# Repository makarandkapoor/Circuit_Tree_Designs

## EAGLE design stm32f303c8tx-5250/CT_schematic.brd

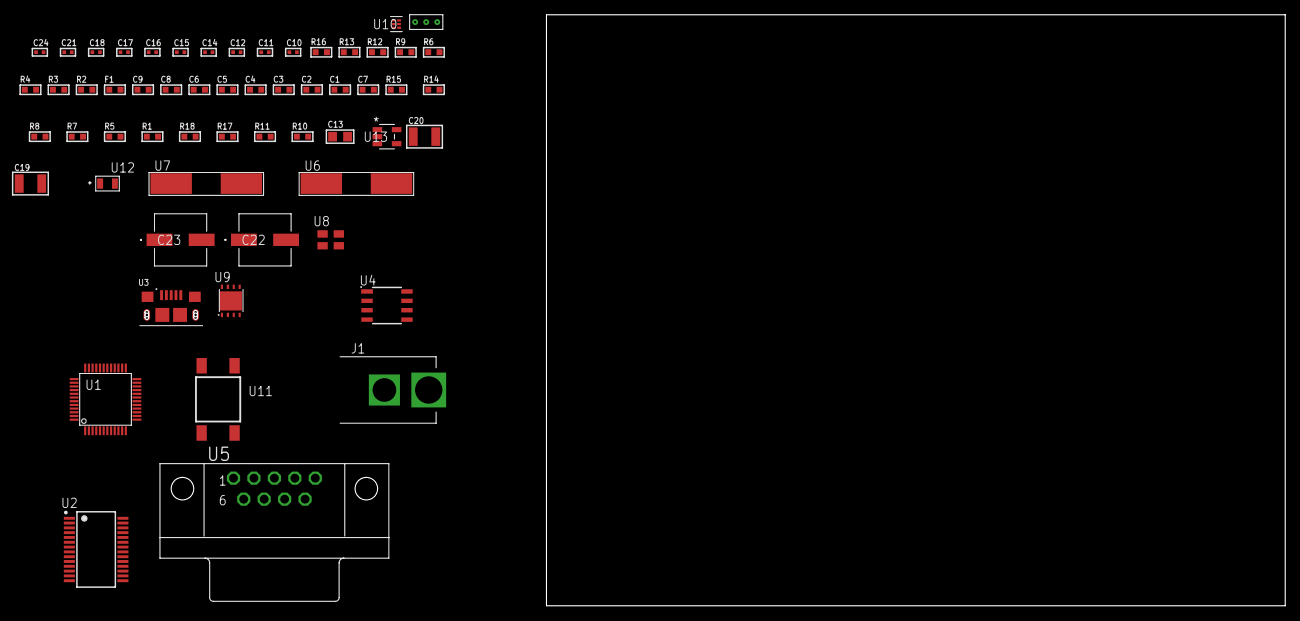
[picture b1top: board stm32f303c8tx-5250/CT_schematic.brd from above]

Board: 2 copper layers, 58 parts (0 on the bottom side), 38 nets, no tracks yet.

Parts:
C1, C9: 1e-06; C0603
C2, C3, C4, C5, C6: 1e-07; C0603
C7: 4.7e-06; C0603
C8: 1e-08; C0603
C10, C11: 1e-11; C0402
C12, C14, C15, C16, C21: 1e-07; C0402
C13: 4.7e-06; C0805
C17, C18, C24: 1e-08; C0402
C19, C20: 1e-05; C1210
C22, C23: 0.0001; EXV-9H
F1: 240.0; L0603
J1: PJ-037B; PJ-037B_PACKAGE
R1, R5, R7, R8, R14, R15: 10000.0; R0603
R2, R13: 1000.0; R0603
R3: 1600.5; R0603
R4, R6: 4700.0; R0603
R9: 120.0; R0603
R10, R11: 100000.0; R0603
R12: 2231.0; R0603
R16: 9100.0; R0603
R17: 680000.0; R0603
R18: 120000.0; R0603
U1: STM32F303C8T6; LQFP48
U2: FT232RL-REEL; SSOP-28
U3: 10118193-0001LF; FCI_10118193-0001LF
U4: SN65HVD230D; SOIC-8
U5: 182-009-113R531; 182-009-MALE
U6: ABLS-25.000MHZ-B2F-T
U7: ABLS-12.000MHZ-B4-T
U8: ASEK-32.768KHz-ECST; ASEK
U9: LP3878SDX-ADJ/NOPB; WSON-8
U10: TPS3895ADRYR; SON-6
U11: 4-1437565-2; SW_4-1437565-2
U12: Q65110A2395; LGM67K-G1J2-24-Z
U13: nc7sz125m5x; NC7SZ125M5X
U14: Dummy; DUMMY_PACKAGE_117

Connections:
CLK_CRYSTAL_U1_5: C10.1, U1.5, U6.1
CLK_CRYSTAL_U1_6: C11.1, U1.6, U6.2
CLK_CRYSTAL_U2_27: U2.27, U7.1
CLK_CRYSTAL_U2_28: U2.28, U7.2
CLK_U1_3: U1.3, U8.3
GND: C1.2, C2.2, C3.2, C4.2, C5.2, C6.2, C7.2, C8.2, C9.2, C10.2, C11.2, C12.2, C13.2, C14.2, C15.2, C16.2, C17.2, C18.2, C19.2, C20.2, C21.2, C22.2, C23.2, C24.2, J1.2, R2.2, R5.2, R8.2, R10.2, R13.2, R16.2, R18.2, U1.8, U1.23, U1.35, U1.47, U2.7, U2.18, U2.21, U2.25, U2.26, U3.5, U3.6, U3.7, U3.8, U3.9, U4.2, U5.5, U8.2, U9.3, U9.PAD, U10.2, U12.C, U13.1, U13.3, U14.1
NET_U1_7: R4.1, U1.7, U13.4
NET_U1_9: C8.1, C9.1, F1.1, U1.9
NET_U1_42: R3.1, U1.42, U12.A
NET_U1_43: R1.1, U1.43, U11.3, U11.4
NET_U1_44: R5.1, U1.44
NET_U2_14: R7.1, U2.14
NET_U2_17: C14.1, U2.17
NET_U2_19: R8.1, U2.19
NET_U3_1: R6.1, U3.1
NET_U3_2: U2.16, U3.2
NET_U3_3: U2.15, U3.3
NET_U4_6: R9.2, U4.6
NET_U4_8: R10.1, U4.8
NET_U5_2: R9.2, U4.6, U5.2
NET_U5_3: R9.1, U4.7, U5.3
NET_U9_1: C18.1, U9.1
NET_U9_6: R12.2, R13.1, U9.6
NET_U9_8: R11.1, U9.8
NET_U10_1: R15.1, R16.1, U10.1
NET_U10_3: R17.2, R18.1, U10.3
NET_U10_4: R14.1, U10.4, U13.2
NET_U11_1: R2.1, U11.1, U11.2
PROC_CAN_RX: U1.45, U4.4
PROC_CAN_TX: U1.46, U4.1
PROC_TIM1_CH1: U1.29, U14.3
PROC_TIM1_CH2N: U1.18, U14.2
PROC_USART1_CTS: U1.32, U2.3
PROC_USART1_RTS: U1.33, U2.11
PROC_USART1_RX: U1.31, U2.1
PROC_USART1_TX: U1.30, U2.5
VCC_S1_11V5: C19.1, C22.1, C23.1, J1.1, R11.2, U9.4
VCC_TIER1_3V3: C1.1, C2.1, C3.1, C4.1, C5.1, C6.1, C7.1, C12.1, C13.1, C15.1, C16.1, C17.1, C20.1, C21.1, C24.1, F1.2, R1.2, R3.2, R4.2, R7.2, R12.1, R14.2, R15.2, R17.1, U1.1, U1.24, U1.36, U1.48, U2.4, U2.20, U4.3, U8.4, U9.5, U10.6, U13.5

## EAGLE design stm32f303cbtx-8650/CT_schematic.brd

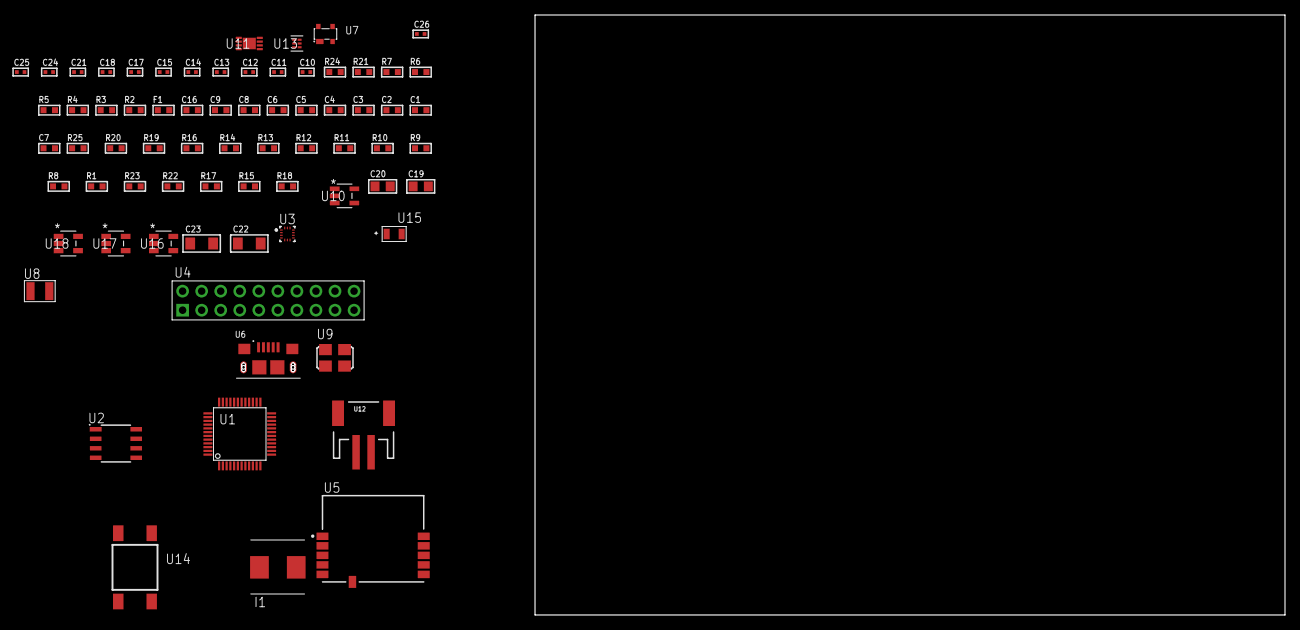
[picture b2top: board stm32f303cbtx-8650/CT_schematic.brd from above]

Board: 2 copper layers, 71 parts (0 on the bottom side), 41 nets, no tracks yet.

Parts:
C1, C9, C16: 1e-06; C0603
C2, C3, C4, C5, C6: 1e-07; C0603
C7: 4.7e-06; C0603
C8: 1e-08; C0603
C10, C11: 1e-11; C0402
C12, C18, C24, C25, C26: 1e-08; C0402
C13, C14, C15, C17, C21: 1e-07; C0402
C19, C20: 1e-05; C0805
C22, C23: 1e-05; C1206
F1: 240.0; L0603
I1: 2e-06; WE-HCI_7030/7040/7050
R1, R8, R9, R10, R11, R12, R13, R14, R19, R20, R25: 10000.0; R0603
R2: 1000.0; R0603
R3: 1600.5; R0603
R4, R5: 4700.0; R0603
R6, R7: 2200.0; R0603
R15: 100000.0; R0603
R16: 47000.0; R0603
R17: 220000.0; R0603
R18: 1000000.0; R0603
R21: 9100.0; R0603
R22: 680000.0; R0603
R23: 120000.0; R0603
R24: 2000.0; R0603
U1: STM32F303CBT6; LQFP48
U2: AT25020B-SSHL-T; SOIC-8
U3: BMC150; LGA14R35P5X6_200X200X100
U4: TST-110-05-T-D-RA
U5: SPBTLE-RF; XCVR_SPBTLE-RF
U6: 10118193-0001LF; FCI_10118193-0001LF
U7: prtr5v0u2ax; SOT143B
U8: ABS07-32.768KHZ-7-T
U9: ASFL1-25MHZ-NCS; ASFL1
U10: ltc3406es5; TSOT-23-5
U11: MCP73831T-2ACI/MC; DFN8_2X3MC
U12: S2B-PH-SM4-TB(LF)(SN); JST-2-SMD
U13: TPS3895ADRYR; SON-6
U14: 4-1437565-2; SW_4-1437565-2
U15: Q65110A2395; LGM67K-G1J2-24-Z
U16, U17, U18: nc7sz125m5x; NC7SZ125M5X

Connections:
CLK_CRYSTAL_U1_3: C10.1, U1.3, U8.1
CLK_CRYSTAL_U1_4: C11.1, U1.4, U8.2
CLK_U1_5: U1.5, U9.3
GND: C1.2, C2.2, C3.2, C4.2, C5.2, C6.2, C7.2, C8.2, C9.2, C10.2, C11.2, C12.2, C13.2, C14.2, C15.2, C16.2, C17.2, C18.2, C19.2, C20.1, C20.2, C21.2, C22.2, C23.2, C24.2, C25.2, C26.2, R2.2, R8.2, R15.2, R16.2, R17.2, R21.2, R23.2, R24.2, U1.8, U1.23, U1.35, U1.47, U2.4, U3.1, U3.6, U3.7, U3.9, U4.4, U4.6, U4.8, U4.10, U4.12, U4.14, U4.16, U4.18, U4.20, U5.6, U6.5, U6.6, U6.7, U6.8, U6.9, U7.1, U9.2, U10.2, U11.6, U11.9, U12.2, U13.2, U15.C, U16.2, U16.3, U17.1, U17.3, U18.1, U18.3
INPUT_USBPOWER_5V: C22.1, R25.2, U6.1, U7.4, U11.1, U11.2
NET_U1_7: R5.1, U1.7, U18.4
NET_U1_9: C8.1, C9.1, F1.1, U1.9
NET_U1_38: R6.1, U1.38, U3.11
NET_U1_43: R7.1, U1.43, U3.14
NET_U1_44: R8.1, U1.44
NET_U1_45: R3.1, U1.45, U15.A
NET_U1_46: R1.1, U1.46, U14.3, U14.4
NET_U2_3: R9.1, U2.3
NET_U2_7: R11.1, U2.7
NET_U5_11: R4.1, U5.11, U17.4
NET_U10_3: I1.1, U10.3
NET_U10_5: R17.1, R18.1, U10.5
NET_U10_ATNET_3: I1.2, R18.2
NET_U11_5: R25.1, U11.5
NET_U11_8: R24.1, U11.8
NET_U13_1: R20.1, R21.1, U13.1
NET_U13_3: R22.2, R23.1, U13.3
NET_U13_4: R19.1, U13.4, U16.4, U17.2, U18.2
NET_U14_1: R2.1, U14.1, U14.2
PROC_GPIO_TO_U5_SPI_IRQ: R16.1, U1.2, U5.4
PROC_SPI1_MISO: U1.16, U5.8
PROC_SPI1_MOSI: U1.17, U5.9
PROC_SPI1_NSS: R14.1, U1.14, U5.10
PROC_SPI1_SCK: R15.1, U1.15, U5.7
PROC_SPI2_MISO: U1.27, U2.2
PROC_SPI2_MOSI: U1.28, U2.5
PROC_SPI2_NSS: R10.1, U1.25, U2.1
PROC_SPI2_SCK: U1.26, U2.6
PROC_SYS_JTCK_SWCLK: U1.37, U4.9
PROC_SYS_JTDO_TRACESWO: U1.39, U4.13
PROC_SYS_JTMS_SWDIO: U1.34, U4.7
PROC_USB_DM: U1.32, U6.2, U7.3
PROC_USB_DP: U1.33, U6.3, U7.2
RST_OUT_U4_SRESET_B: R13.1, U4.15, U16.1
VCC_S1_3V7: C19.1, C23.1, U10.4, U11.3, U11.4, U12.1
VCC_TIER1_3V3: C1.1, C2.1, C3.1, C4.1, C5.1, C6.1, C7.1, C12.1, C13.1, C14.1, C15.1, C16.1, C17.1, C18.1, C20.2, C21.1, C24.1, C25.1, C26.1, F1.2, I1.2, R1.2, R3.2, R4.2, R5.2, R6.2, R7.2, R9.2, R10.2, R11.2, R12.1, R12.2, R13.2, R14.2, R18.2, R19.2, R20.2, R22.1, U1.1, U1.24, U1.36, U1.48, U2.8, U3.8, U3.10, U3.12, U3.13, U4.1, U5.5, U9.4, U13.6, U16.5, U17.5, U18.5

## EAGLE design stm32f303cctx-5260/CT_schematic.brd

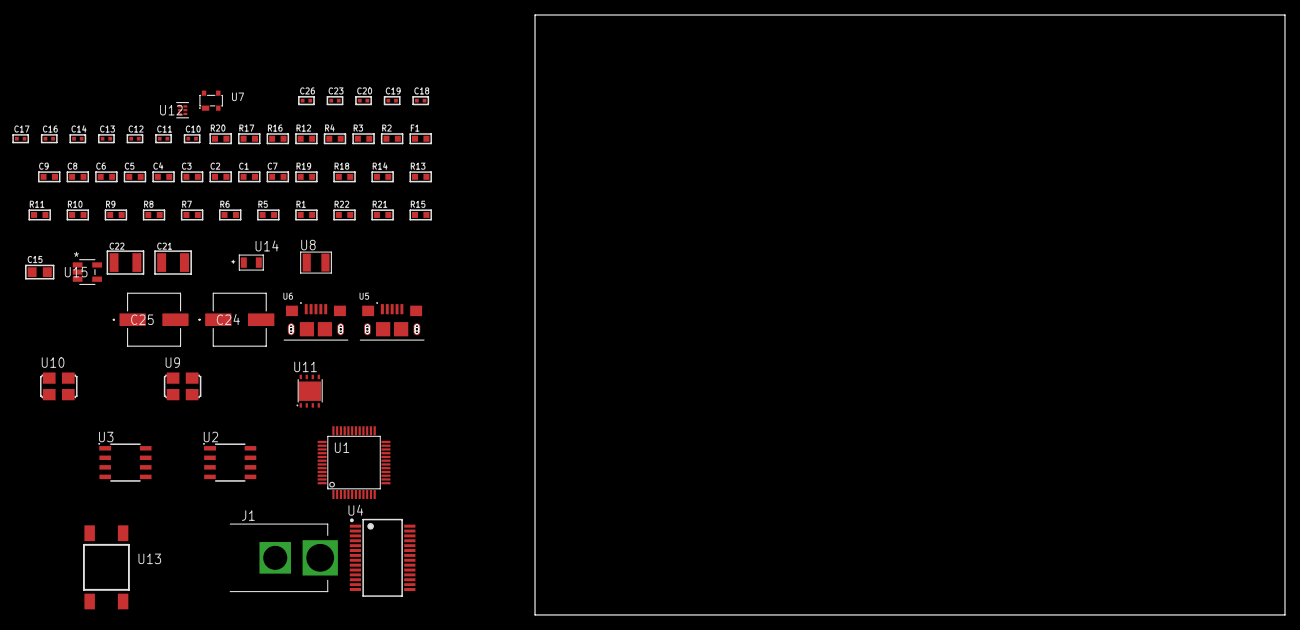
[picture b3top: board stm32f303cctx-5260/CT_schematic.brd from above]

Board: 2 copper layers, 65 parts (0 on the bottom side), 44 nets, no tracks yet.

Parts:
C1, C9: 1e-06; C0603
C2, C3, C4, C5, C6: 1e-07; C0603
C7: 4.7e-06; C0603
C8: 1e-08; C0603
C10, C11: 1e-11; C0402
C12, C13, C18, C19, C20, C26: 1e-08; C0402
C14, C16, C17, C23: 1e-07; C0402
C15: 4.7e-06; C0805
C21, C22: 1e-05; C1210
C24, C25: 0.0001; EXV-9H
F1: 240.0; L0603
J1: PJ-037B; PJ-037B_PACKAGE
R1, R5, R6, R7, R8, R9, R10, R11, R13, R14, R18, R19: 10000.0; R0603
R2, R17: 1000.0; R0603
R3: 1600.5; R0603
R4, R12: 4700.0; R0603
R15: 100000.0; R0603
R16: 2231.0; R0603
R20: 9100.0; R0603
R21: 680000.0; R0603
R22: 120000.0; R0603
U1: STM32F303CCT6; LQFP48
U2: AT25320B-SSHL-T; SOIC-8
U3: AT25512N-SH-T; SOIC-8
U4: FT232RL-REEL; SSOP-28
U5, U6: 10118193-0001LF; FCI_10118193-0001LF
U7: prtr5v0u2ax; SOT143B
U8: ABS07-32.768KHZ-7-T
U9: ASFL1-12MHZ-NCS; ASFL1
U10: ASFL1-25MHZ-NCS; ASFL1
U11: LP3878SDX-ADJ/NOPB; WSON-8
U12: TPS3895ADRYR; SON-6
U13: 4-1437565-2; SW_4-1437565-2
U14: Q65110A2395; LGM67K-G1J2-24-Z
U15: nc7sz125m5x; NC7SZ125M5X

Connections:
CLK_CRYSTAL_U1_3: C10.1, U1.3, U8.1
CLK_CRYSTAL_U1_4: C11.1, U1.4, U8.2
CLK_U1_5: U1.5, U10.3
CLK_U4_27: U4.27, U9.3
GND: C1.2, C2.2, C3.2, C4.2, C5.2, C6.2, C7.2, C8.2, C9.2, C10.2, C11.2, C12.2, C13.2, C14.2, C15.2, C16.2, C17.2, C18.2, C19.2, C20.2, C21.2, C22.2, C23.2, C24.2, C25.2, C26.2, J1.2, R2.2, R5.2, R14.2, R17.2, R20.2, R22.2, U1.8, U1.23, U1.35, U1.47, U2.4, U3.4, U4.7, U4.18, U4.21, U4.25, U4.26, U5.5, U5.6, U5.7, U5.8, U5.9, U6.5, U6.6, U6.7, U6.8, U6.9, U7.1, U9.2, U10.2, U11.3, U11.PAD, U12.2, U14.C, U15.1, U15.3
NET_U1_7: R4.1, U1.7, U15.4
NET_U1_9: C8.1, C9.1, F1.1, U1.9
NET_U1_44: R5.1, U1.44
NET_U1_45: R3.1, U1.45, U14.A
NET_U1_46: R1.1, U1.46, U13.3, U13.4
NET_U2_3: R6.1, U2.3
NET_U2_7: R8.1, U2.7
NET_U3_3: R9.1, U3.3
NET_U3_7: R11.1, U3.7
NET_U4_14: R13.1, U4.14
NET_U4_17: C16.1, U4.17
NET_U4_19: R14.1, U4.19
NET_U5_1: R12.1, U5.1
NET_U5_2: U4.16, U5.2
NET_U5_3: U4.15, U5.3
NET_U7_4: U6.1, U7.4
NET_U11_1: C20.1, U11.1
NET_U11_6: R16.2, R17.1, U11.6
NET_U11_8: R15.1, U11.8
NET_U12_1: R19.1, R20.1, U12.1
NET_U12_3: R21.2, R22.1, U12.3
NET_U12_4: R18.1, U12.4, U15.2
NET_U13_1: R2.1, U13.1, U13.2
PROC_SPI1_MISO: U1.16, U2.2
PROC_SPI1_MOSI: U1.17, U2.5
PROC_SPI1_NSS: R7.1, U1.14, U2.1
PROC_SPI1_SCK: U1.15, U2.6
PROC_SPI2_MISO: U1.27, U3.2
PROC_SPI2_MOSI: U1.28, U3.5
PROC_SPI2_NSS: R10.1, U1.25, U3.1
PROC_SPI2_SCK: U1.26, U3.6
PROC_USART2_CTS: U1.10, U4.3
PROC_USART2_RTS: U1.11, U4.11
PROC_USART2_RX: U1.13, U4.1
PROC_USART2_TX: U1.12, U4.5
PROC_USB_DM: U1.32, U6.2, U7.3
PROC_USB_DP: U1.33, U6.3, U7.2
VCC_S1_12V1: C21.1, C24.1, C25.1, J1.1, R15.2, U11.4
VCC_TIER1_3V3: C1.1, C2.1, C3.1, C4.1, C5.1, C6.1, C7.1, C12.1, C13.1, C14.1, C15.1, C17.1, C18.1, C19.1, C22.1, C23.1, C26.1, F1.2, R1.2, R3.2, R4.2, R6.2, R7.2, R8.2, R9.2, R10.2, R11.2, R13.2, R16.1, R18.2, R19.2, R21.1, U1.1, U1.24, U1.36, U1.48, U2.8, U3.8, U4.4, U4.20, U9.4, U10.4, U11.5, U12.6, U15.5

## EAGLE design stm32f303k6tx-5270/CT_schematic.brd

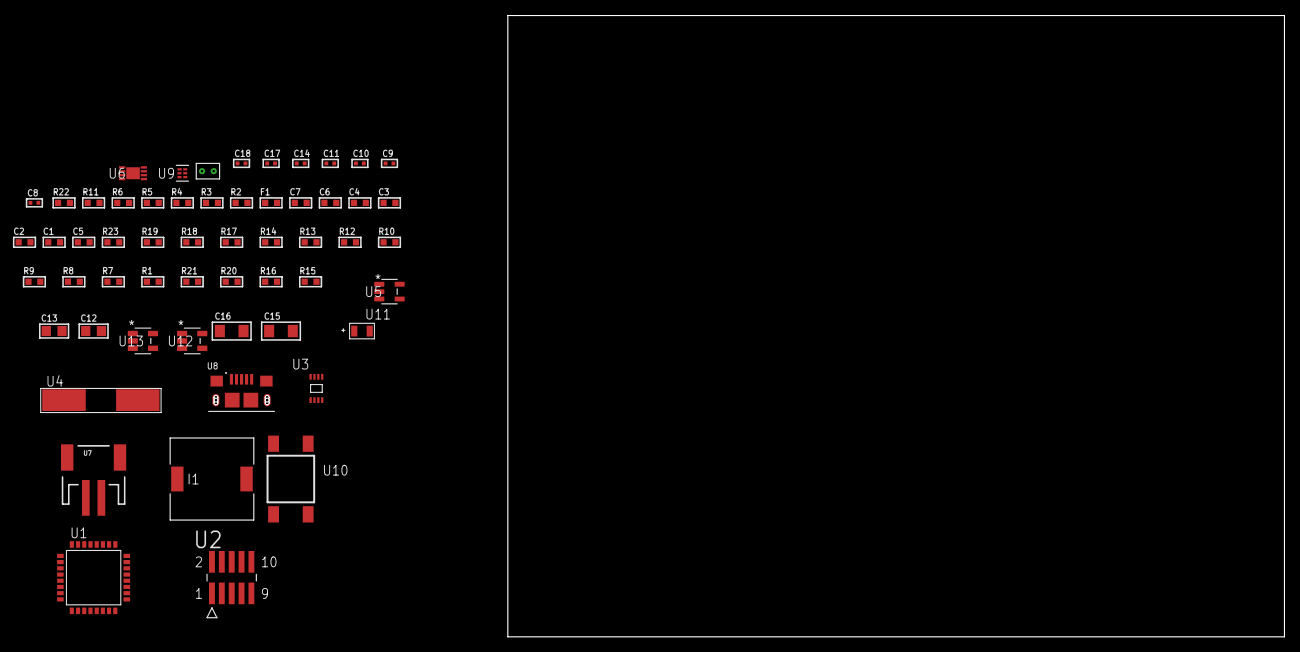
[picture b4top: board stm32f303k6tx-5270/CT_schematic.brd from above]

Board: 2 copper layers, 57 parts (0 on the bottom side), 31 nets, no tracks yet.

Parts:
C1, C2, C3, C4: 1e-07; C0603
C5: 4.7e-06; C0603
C6: 1e-08; C0603
C7: 1e-06; C0603
C8, C9: 1e-11; C0402
C10, C14: 1e-07; C0402
C11, C17, C18: 1e-08; C0402
C12, C13: 1e-05; C0805
C15, C16: 1e-05; C1206
F1: 240.0; L0603
I1: 5.2e-06; DR1040
R1, R7, R8, R9, R10, R12, R13, R14, R17, R18, R23: 10000.0; R0603
R2: 1000.0; R0603
R3: 1270.0; R0603
R4: 4700.0; R0603
R5, R6: 2200.0; R0603
R11: 5.0; R0603
R15: 309473.68421053; R0603
R16: 1000000.0; R0603
R19: 18000.0; R0603
R20: 470000.0; R0603
R21: 120000.0; R0603
R22: 2000.0; R0603
U1: STM32F303K6T6; LQFP32
U2: FTSH-105-01-L-DV-K; SAMTEC_FTSH-105-01-L-DV-K
U3: 24AA32AT-I/MNY; TDFN-8/6MM
U4: ABLS-25.000MHZ-B2F-T
U5: ltc3406es5; TSOT-23-5
U6: MCP73831T-2ACI/MC; DFN8_2X3MC
U7: S2B-PH-SM4-TB(LF)(SN); JST-2-SMD
U8: 10118193-0001LF; FCI_10118193-0001LF
U9: TPS3895ADRYR; SON-6
U10: 4-1437565-2; SW_4-1437565-2
U11: Q65110A2395; LGM67K-G1J2-24-Z
U12, U13: nc7sz125m5x; NC7SZ125M5X
U14: Dummy; DUMMY_PACKAGE_119

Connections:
CLK_CRYSTAL_U1_2: C8.1, U1.2, U4.1
CLK_CRYSTAL_U1_3: C9.1, U1.3, U4.2
GND: C1.2, C2.2, C3.2, C4.2, C5.2, C6.2, C7.2, C8.2, C9.2, C10.2, C11.2, C12.2, C13.1, C13.2, C14.2, C15.2, C16.2, C17.2, C18.2, R2.2, R7.2, R11.2, R12.2, R14.2, R15.2, R19.2, R21.2, R22.2, U1.16, U1.32, U2.3, U2.5, U3.4, U5.2, U6.6, U6.9, U7.2, U8.5, U8.6, U8.7, U8.8, U8.9, U9.2, U11.C, U12.2, U12.3, U13.1, U13.3, U14.1
INPUT_USBPOWER_5V: C15.1, R23.2, U6.1, U6.2, U8.1
NET_U1_4: R4.1, U1.4, U13.4
NET_U1_5: C6.1, C7.1, F1.1, U1.5
NET_U1_25: R5.1, U1.25, U3.6
NET_U1_28: R3.1, U1.28, U11.A
NET_U1_29: R1.1, U1.29, U10.3, U10.4
NET_U1_30: R6.1, U1.30, U3.5
NET_U1_31: R7.1, U1.31
NET_U2_9: R11.1, U2.9
NET_U3_1: R12.1, U3.1
NET_U3_2: R13.1, U3.2
NET_U3_3: R14.1, U3.3
NET_U5_3: I1.1, U5.3
NET_U5_5: R15.1, R16.1, U5.5
NET_U5_ATNET_3: I1.2, R16.2
NET_U6_5: R23.1, U6.5
NET_U6_8: R22.1, U6.8
NET_U9_1: R18.1, R19.1, U9.1
NET_U9_3: R20.2, R21.1, U9.3
NET_U9_4: R17.1, U9.4, U12.4, U13.2
NET_U10_1: R2.1, U10.1, U10.2
PROC_DAC1_OUT2: U1.11, U14.2
PROC_SYS_JTCK_SWCLK: R9.1, U1.24, U2.4
PROC_SYS_JTDO_TRACESWO: U1.26, U2.6
PROC_SYS_JTMS_SWDIO: R10.1, U1.23, U2.2
RST_OUT_U2_JTAG_RST_B: R8.1, U2.10, U12.1
VCC_S1_3V7: C12.1, C16.1, U5.4, U6.3, U6.4, U7.1
VCC_TIER1_2V5: C1.1, C2.1, C3.1, C4.1, C5.1, C10.1, C11.1, C13.2, C14.1, C17.1, C18.1, F1.2, I1.2, R1.2, R3.2, R4.2, R5.2, R6.2, R8.2, R9.2, R10.2, R13.2, R16.2, R17.2, R18.2, R20.1, U1.1, U1.17, U2.1, U3.7, U3.8, U9.6, U12.5, U13.5

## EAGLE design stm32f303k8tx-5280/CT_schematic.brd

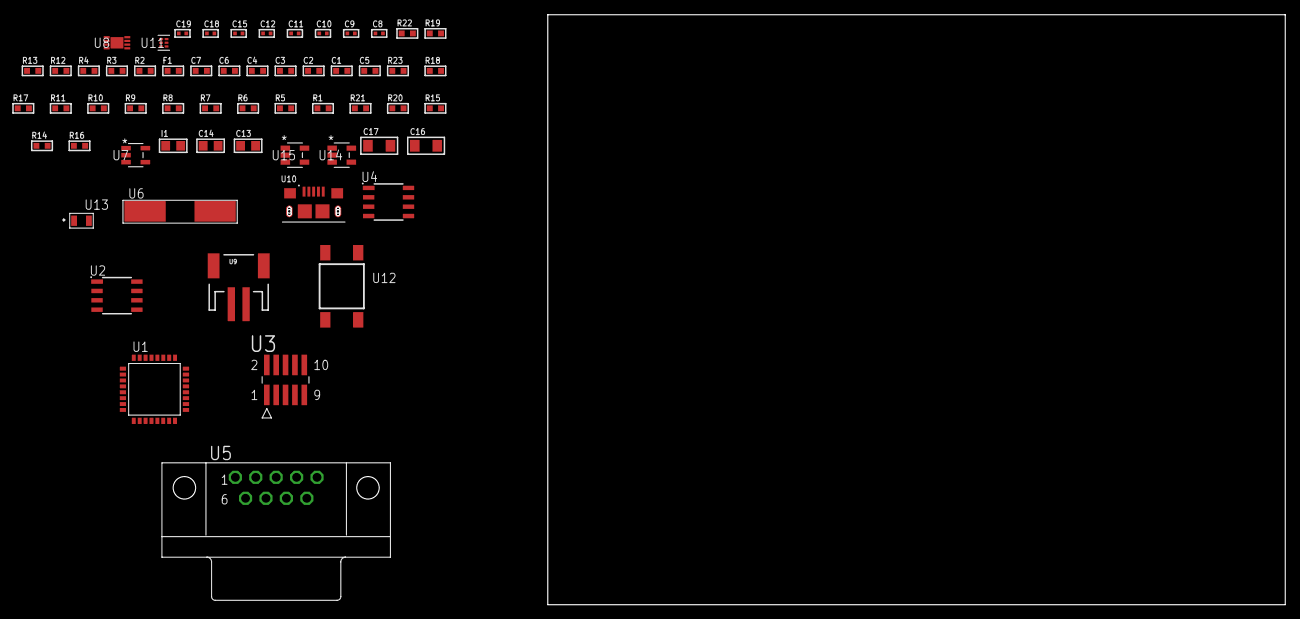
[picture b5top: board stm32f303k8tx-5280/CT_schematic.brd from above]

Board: 2 copper layers, 59 parts (0 on the bottom side), 37 nets, no tracks yet.

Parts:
C1, C2, C3, C4: 1e-07; C0603
C5: 4.7e-06; C0603
C6: 1e-08; C0603
C7: 1e-06; C0603
C8, C9: 1e-11; C0402
C10, C18, C19: 1e-08; C0402
C11, C12, C15: 1e-07; C0402
C13, C14: 1e-05; C0805
C16, C17: 1e-05; C1206
F1: 240.0; L0603
I1: 2.2e-06; L0805
R1, R5, R6, R7, R8, R9, R10, R11, R17, R18, R23: 10000.0; R0603
R2: 1000.0; R0603
R3: 1600.5; R0603
R4: 4700.0; R0603
R12: 5.0; R0603
R13: 120.0; R0603
R14: 470000.0; R0603
R15: 220000.0; R0603
R16: 1000000.0; R0603
R19: 9100.0; R0603
R20: 680000.0; R0603
R21: 120000.0; R0603
R22: 2000.0; R0603
U1: STM32F303K8T6; LQFP32
U2: AT25160B-SSHL-T; SOIC-8
U3: FTSH-105-01-L-DV-K; SAMTEC_FTSH-105-01-L-DV-K
U4: SN65HVD230D; SOIC-8
U5: 182-009-113R531; 182-009-MALE
U6: ABLS-25.000MHZ-B2F-T
U7: ltc3406es5; TSOT-23-5
U8: MCP73831T-2ACI/MC; DFN8_2X3MC
U9: S2B-PH-SM4-TB(LF)(SN); JST-2-SMD
U10: 10118193-0001LF; FCI_10118193-0001LF
U11: TPS3895ADRYR; SON-6
U12: 4-1437565-2; SW_4-1437565-2
U13: Q65110A2395; LGM67K-G1J2-24-Z
U14, U15: nc7sz125m5x; NC7SZ125M5X

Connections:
CLK_CRYSTAL_U1_2: C8.1, U1.2, U6.1
CLK_CRYSTAL_U1_3: C9.1, U1.3, U6.2
GND: C1.2, C2.2, C3.2, C4.2, C5.2, C6.2, C7.2, C8.2, C9.2, C10.2, C11.2, C12.2, C13.2, C14.1, C14.2, C15.2, C16.2, C17.2, C18.2, C19.2, R2.2, R5.2, R12.2, R14.2, R15.2, R19.2, R21.2, R22.2, U1.16, U1.32, U2.4, U3.3, U3.5, U4.2, U5.5, U7.2, U8.6, U8.9, U9.2, U10.5, U10.6, U10.7, U10.8, U10.9, U11.2, U13.C, U14.2, U14.3, U15.1, U15.3
INPUT_USBPOWER_5V: C16.1, R23.2, U8.1, U8.2, U10.1
NET_U1_4: R4.1, U1.4, U15.4
NET_U1_5: C6.1, C7.1, F1.1, U1.5
NET_U1_29: R3.1, U1.29, U13.A
NET_U1_30: R1.1, U1.30, U12.3, U12.4
NET_U1_31: R5.1, U1.31
NET_U2_3: R6.1, U2.3
NET_U2_7: R8.1, U2.7
NET_U3_9: R12.1, U3.9
NET_U4_6: R13.2, U4.6
NET_U4_8: R14.1, U4.8
NET_U5_2: R13.2, U4.6, U5.2
NET_U5_3: R13.1, U4.7, U5.3
NET_U7_3: I1.1, U7.3
NET_U7_5: R15.1, R16.1, U7.5
NET_U7_ATNET_3: I1.2, R16.2
NET_U8_5: R23.1, U8.5
NET_U8_8: R22.1, U8.8
NET_U11_1: R18.1, R19.1, U11.1
NET_U11_3: R20.2, R21.1, U11.3
NET_U11_4: R17.1, U11.4, U14.4, U15.2
NET_U12_1: R2.1, U12.1, U12.2
PROC_CAN_RX: U1.21, U4.4
PROC_CAN_TX: U1.22, U4.1
PROC_SPI1_MISO: U1.12, U2.2
PROC_SPI1_MOSI: U1.13, U2.5
PROC_SPI1_NSS: R7.1, U1.10, U2.1
PROC_SPI1_SCK: U1.11, U2.6
PROC_SYS_JTCK_SWCLK: R10.1, U1.24, U3.4
PROC_SYS_JTDO_TRACESWO: U1.26, U3.6
PROC_SYS_JTMS_SWDIO: R11.1, U1.23, U3.2
RST_OUT_U3_JTAG_RST_B: R9.1, U3.10, U14.1
VCC_S1_3V7: C13.1, C17.1, U7.4, U8.3, U8.4, U9.1
VCC_TIER1_3V3: C1.1, C2.1, C3.1, C4.1, C5.1, C10.1, C11.1, C12.1, C14.2, C15.1, C18.1, C19.1, F1.2, I1.2, R1.2, R3.2, R4.2, R6.2, R7.2, R8.2, R9.2, R10.2, R11.2, R16.2, R17.2, R18.2, R20.1, U1.1, U1.17, U2.8, U3.1, U4.3, U11.6, U14.5, U15.5

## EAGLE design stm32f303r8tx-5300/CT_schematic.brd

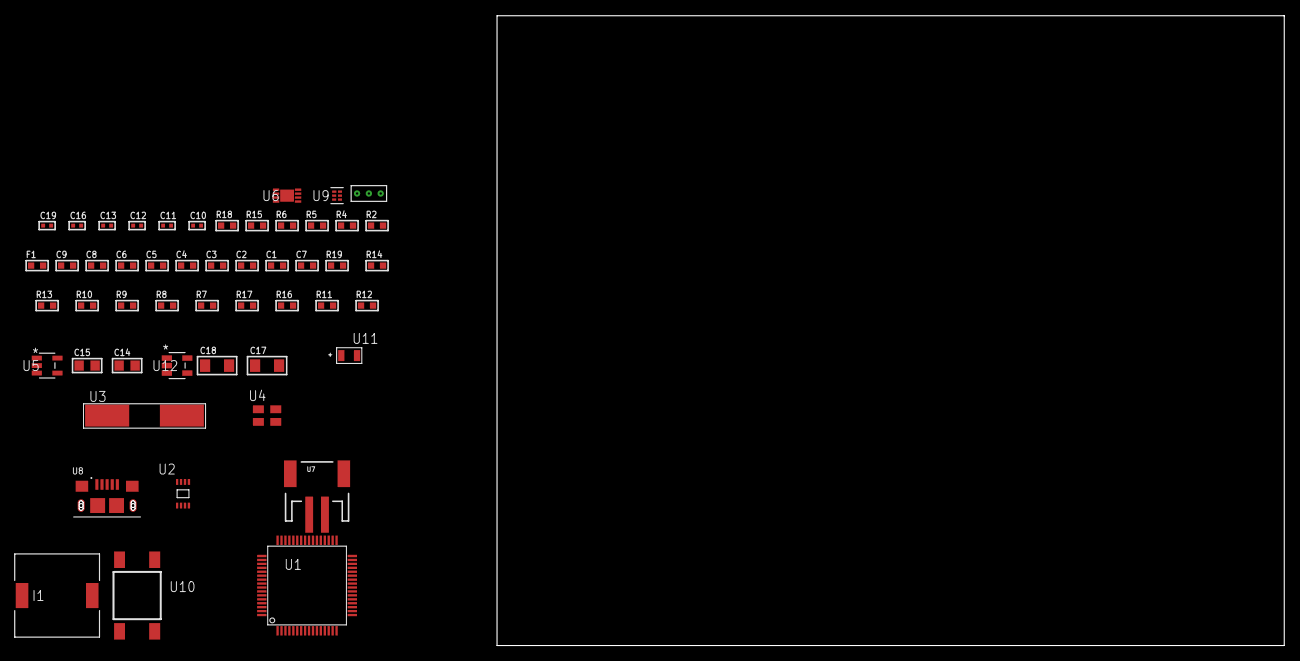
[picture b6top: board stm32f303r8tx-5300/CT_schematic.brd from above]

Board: 2 copper layers, 153.1 x 80.0 mm, 51 parts (0 on the bottom side), 27 nets, no tracks yet.

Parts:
C1, C9: 1e-06; C0603
C2, C3, C4, C5, C6: 1e-07; C0603
C7: 4.7e-06; C0603
C8: 1e-08; C0603
C10, C11: 1e-11; C0402
C12, C13, C19: 1e-08; C0402
C14, C15: 1e-05; C0805
C16: 1e-07; C0402
C17, C18: 1e-05; C1206
F1: 240.0; L0603
I1: 2.5e-06; DR1040
R2: 1000.0; R0603
R4: 4700.0; R0603
R5, R6: 2200.0; R0603
R7, R8, R9, R10, R13, R14, R19: 10000.0; R0603
R11: 220000.0; R0603
R12: 1000000.0; R0603
R15: 9100.0; R0603
R16: 680000.0; R0603
R17: 120000.0; R0603
R18: 2000.0; R0603
U1: STM32F303R8T6; LQFP64
U2: 24AA32AT-I/MNY; TDFN-8/6MM
U3: ABLS-25.000MHZ-B2F-T
U4: ASEK-32.768KHz-ECST; ASEK
U5: ltc3406es5; TSOT-23-5
U6: MCP73831T-2ACI/MC; DFN8_2X3MC
U7: S2B-PH-SM4-TB(LF)(SN); JST-2-SMD
U8: 10118193-0001LF; FCI_10118193-0001LF
U9: TPS3895ADRYR; SON-6
U10: 4-1437565-2; SW_4-1437565-2
U11: Q65110A2395; LGM67K-G1J2-24-Z
U12: nc7sz125m5x; NC7SZ125M5X
U13: Dummy; DUMMY_PACKAGE_108

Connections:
CLK_CRYSTAL_U1_5: C10.1, U1.5, U3.1
CLK_CRYSTAL_U1_6: C11.1, U1.6, U3.2
CLK_U1_3: U1.3, U4.3
GND: C1.2, C2.2, C3.2, C4.2, C5.2, C6.2, C7.2, C8.2, C9.2, C10.2, C11.2, C12.2, C13.2, C14.2, C15.1, C15.2, C16.2, C17.2, C18.2, C19.2, R2.2, R7.2, R10.2, R11.2, R15.2, R17.2, R18.2, U1.12, U1.18, U1.31, U1.47, U1.63, U2.4, U4.2, U5.2, U6.6, U6.9, U7.2, U8.5, U8.6, U8.7, U8.8, U8.9, U9.2, U11.C, U12.1, U12.3, U13.1
INPUT_USBPOWER_5V: C17.1, R19.2, U6.1, U6.2, U8.1
NET_U1_7: R4.1, U1.7, U12.4
NET_U1_13: C8.1, C9.1, F1.1, U1.13
NET_U1_49: R6.1, U1.49, U2.5
NET_U1_50: R5.1, U1.50, U2.6
NET_U1_60: R7.1, U1.60
NET_U1_62: U10.3, U10.4
NET_U2_1: R8.1, U2.1
NET_U2_2: R9.1, U2.2
NET_U2_3: R10.1, U2.3
NET_U5_3: I1.1, U5.3
NET_U5_5: R11.1, R12.1, U5.5
NET_U5_ATNET_3: I1.2, R12.2
NET_U6_5: R19.1, U6.5
NET_U6_8: R18.1, U6.8
NET_U9_1: R14.1, R15.1, U9.1
NET_U9_3: R16.2, R17.1, U9.3
NET_U9_4: R13.1, U9.4, U12.2
NET_U10_1: R2.1, U10.1, U10.2
PROC_PC13: U1.2, U13.2
PROC_PC15_OSC32_OUT: U1.4, U13.3
VCC_S1_3V7: C14.1, C18.1, U5.4, U6.3, U6.4, U7.1
VCC_TIER1_3V3: C1.1, C2.1, C3.1, C4.1, C5.1, C6.1, C7.1, C12.1, C13.1, C15.2, C16.1, C19.1, F1.2, I1.2, R4.2, R5.2, R6.2, R8.2, R9.2, R12.2, R13.2, R14.2, R16.1, U1.1, U1.19, U1.32, U1.48, U1.64, U2.7, U2.8, U4.4, U9.6, U12.5

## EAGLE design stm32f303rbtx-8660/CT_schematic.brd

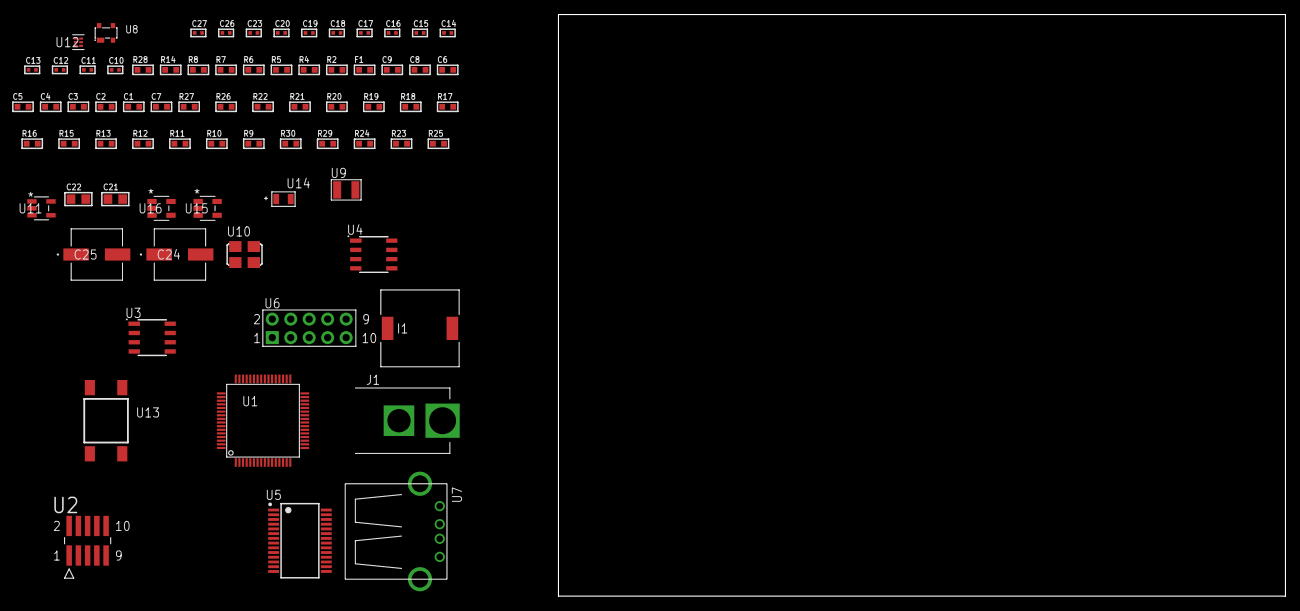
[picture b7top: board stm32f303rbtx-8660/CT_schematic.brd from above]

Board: 2 copper layers, 100.0 x 80.0 mm, 74 parts (0 on the bottom side), 51 nets, no tracks yet.

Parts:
C1, C9: 1e-06; C0603
C2, C3, C4, C5, C6: 1e-07; C0603
C7: 4.7e-06; C0603
C8: 1e-08; C0603
C10, C11: 1e-11; C0402
C12, C15, C16, C17, C18, C19, C23: 1e-07; C0402
C13, C14, C20, C26, C27: 1e-08; C0402
C21, C22: 1e-05; C0805
C24, C25: 0.0001; EXV-9H
F1: 240.0; L0603
I1: 5.2e-06; DR1040
J1: PJ-037B; PJ-037B_PACKAGE
R2: 1000.0; R0603
R4: 4700.0; R0603
R5, R6, R7, R8: 2200.0; R0603
R9, R10, R11, R12, R13, R15, R16, R17, R18, R19, R20, R21, R22, R26, R27: 10000.0; R0603
R14: 5.0; R0603
R23: 100000.0; R0603
R24: 220000.0; R0603
R25: 1000000.0; R0603
R28: 9100.0; R0603
R29: 680000.0; R0603
R30: 120000.0; R0603
U1: STM32F303RBT6; LQFP64
U2: FTSH-105-01-L-DV-K; SAMTEC_FTSH-105-01-L-DV-K
U3, U4: AT24C02D-SSHM-T; AT24C02D
U5: ST3241EBPR; SSOP-28
U6: HTSS-105-01-G-D
U7: 61400416021; USB-A-H
U8: prtr5v0u2ax; SOT143B
U9: ABS07-32.768KHZ-7-T
U10: ASFL1-25MHZ-NCS; ASFL1
U11: ltc3406es5; TSOT-23-5
U12: TPS3895ADRYR; SON-6
U13: 4-1437565-2; SW_4-1437565-2
U14: Q65110A2395; LGM67K-G1J2-24-Z
U15, U16: nc7sz125m5x; NC7SZ125M5X

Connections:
CLK_CRYSTAL_U1_3: C10.1, U1.3, U9.1
CLK_CRYSTAL_U1_4: C11.1, U1.4, U9.2
CLK_U1_5: U1.5, U10.3
GND: C1.2, C2.2, C3.2, C4.2, C5.2, C6.2, C7.2, C8.2, C9.2, C10.2, C11.2, C12.2, C13.2, C14.2, C15.2, C18.2, C19.2, C20.2, C21.2, C22.1, C22.2, C23.2, C24.2, C25.2, C26.2, C27.2, J1.2, R2.2, R9.2, R13.2, R14.2, R15.2, R17.2, R18.2, R19.2, R21.2, R22.2, R24.2, R28.2, R30.2, U1.12, U1.31, U1.47, U1.63, U2.3, U2.5, U3.4, U4.4, U5.23, U5.25, U6.9, U7.4, U7.5, U7.6, U8.1, U10.2, U11.2, U12.2, U14.C, U15.2, U15.3, U16.1, U16.3
NET_U1_6: R7.1, U1.6, U4.6
NET_U1_7: R4.1, U1.7, U16.4
NET_U1_13: C8.1, C9.1, F1.1, U1.13
NET_U1_43: R8.1, U1.43, U4.5
NET_U1_58: R5.1, U1.58, U3.6
NET_U1_59: R6.1, U1.59, U3.5
NET_U1_60: R9.1, U1.60
NET_U1_62: U13.3, U13.4
NET_U2_9: R14.1, U2.9
NET_U3_1: R16.1, U3.1
NET_U3_2: R17.1, U3.2
NET_U3_3: R18.1, U3.3
NET_U3_7: R15.1, U3.7
NET_U4_1: R20.1, U4.1
NET_U4_2: R21.1, U4.2
NET_U4_3: R22.1, U4.3
NET_U4_7: R19.1, U4.7
NET_U5_1: C17.1, U5.1
NET_U5_2: C17.2, U5.2
NET_U5_3: C19.1, U5.3
NET_U5_22: R23.1, U5.22
NET_U5_24: C16.2, U5.24
NET_U5_27: C18.1, U5.27
NET_U5_28: C16.1, U5.28
NET_U6_3: U5.4, U6.3
NET_U6_4: U5.5, U6.4
NET_U6_5: U5.9, U6.5
NET_U6_6: U5.10, U6.6
NET_U8_4: U7.1, U8.4
NET_U11_3: I1.1, U11.3
NET_U11_5: R24.1, R25.1, U11.5
NET_U11_ATNET_3: I1.2, R25.2
NET_U12_1: R27.1, R28.1, U12.1
NET_U12_3: R29.2, R30.1, U12.3
NET_U12_4: R26.1, U12.4, U15.4, U16.2
NET_U13_1: R2.1, U13.1, U13.2
PROC_SYS_JTCK_SWCLK: R13.1, U1.49, U2.4
PROC_SYS_JTDI: R11.1, U1.50, U2.8
PROC_SYS_JTDO_TRACESWO: U1.55, U2.6
PROC_SYS_JTMS_SWDIO: R12.1, U1.46, U2.2
PROC_UART4_RX: U1.52, U5.19
PROC_UART4_TX: U1.51, U5.14
PROC_USB_DM: U7.2, U8.3
PROC_USB_DP: U7.3, U8.2
RST_OUT_U2_JTAG_RST_B: R10.1, U2.10, U15.1
VCC_S1_5V2: C21.1, C24.1, C25.1, J1.1, U11.4
VCC_TIER1_3V3: C1.1, C2.1, C3.1, C4.1, C5.1, C6.1, C7.1, C12.1, C13.1, C14.1, C15.1, C20.1, C22.2, C23.1, C26.1, C27.1, F1.2, I1.2, R4.2, R5.2, R6.2, R7.2, R8.2, R10.2, R11.2, R12.2, R16.2, R20.2, R23.2, R25.2, R26.2, R27.2, R29.1, U1.1, U1.19, U1.32, U1.48, U1.64, U2.1, U3.8, U4.8, U5.26, U10.4, U12.6, U15.5, U16.5
